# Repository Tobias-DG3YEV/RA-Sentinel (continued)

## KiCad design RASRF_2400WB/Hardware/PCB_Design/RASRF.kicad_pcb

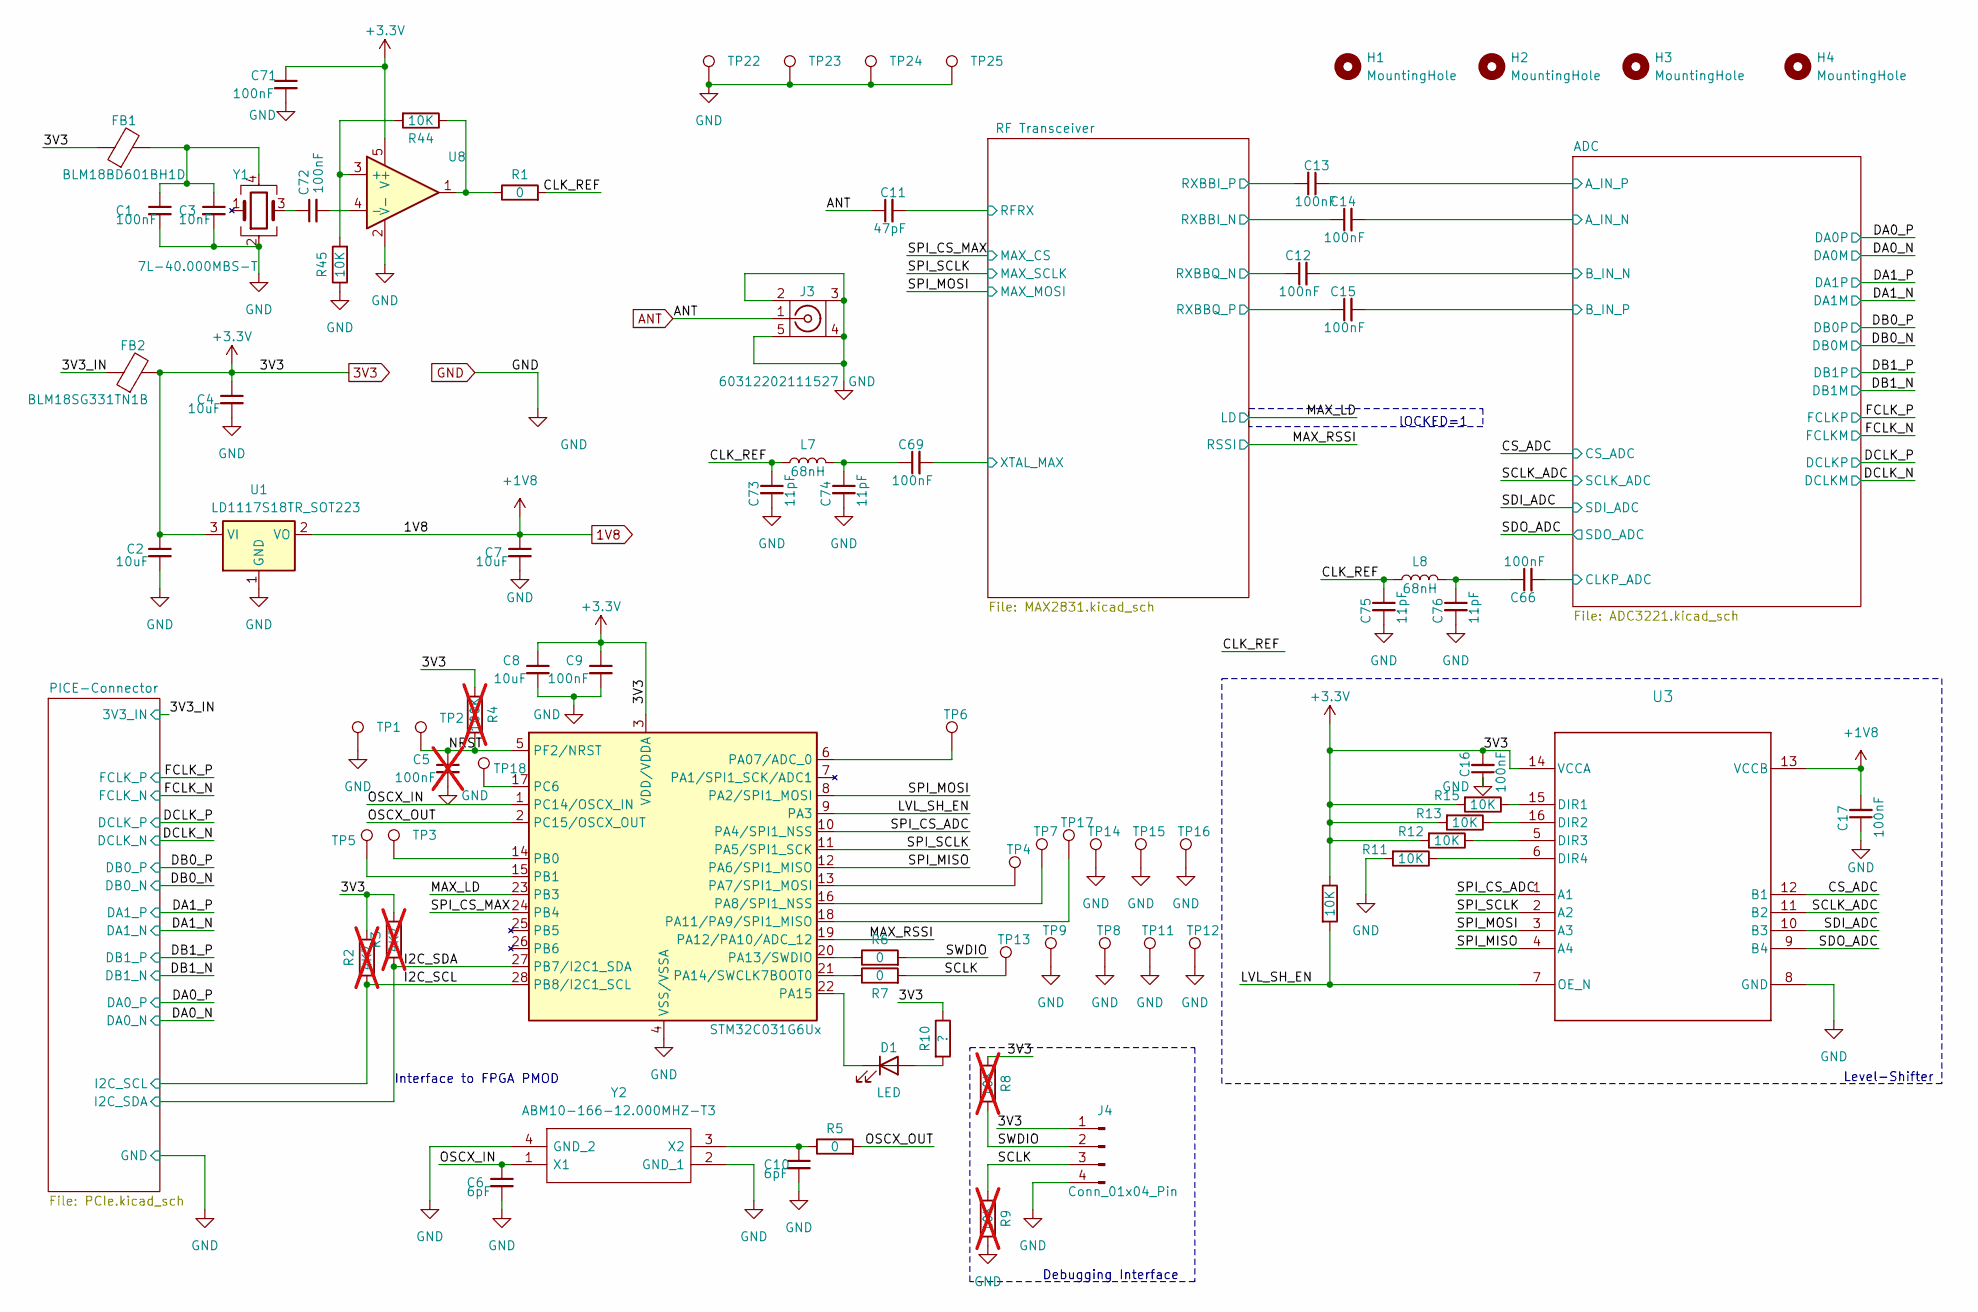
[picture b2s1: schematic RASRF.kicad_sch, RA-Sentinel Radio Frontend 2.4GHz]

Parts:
C1, C9, C12, C13, C14, C15, C16, C17, C66, C69, C71, C72: 100nF; C_0603_1608Metric
C2, C4, C7, C8: 10uF; C_0603_1608Metric
C3: 10nF; C_0603_1608Metric
C5: 100nF; C_0603_1608Metric; not fitted
C6, C10: 6pF; C_0603_1608Metric
C11: 47pF; C_0603_1608Metric
C73, C74, C75, C76: 11pF; C_0603_1608Metric
D1: LED; LED_0603_1608Metric
FB1: BLM18BD601BH1D; IND_BLM18_0603_MUR
FB2: BLM18SG331TN1B; IND_BLM18_0603_MUR
H1, H2, H3, H4: MountingHole; MountingHole_3.2mm_M3_ISO7380
J3: 60312202111527; JACK_02114307_WRE
J4: Conn_01x04_Pin; PinSocket_1x04_P2.54mm_Vertical
L7, L8: 68nH; L_0603_1608Metric
R1, R5, R6, R7: 0; R_0603_1608Metric
R2, R3: 4K7; R_0603_1608Metric; not fitted
R4: 100K; R_0603_1608Metric; not fitted
R8, R9: 10K; R_0603_1608Metric; not fitted
R10: ?; R_0603_1608Metric
R11, R12, R13, R14, R15, R44, R45: 10K; R_0603_1608Metric
TP1, TP8, TP11, TP12, TP14, TP15, TP16: TestPoint; TestPoint_THTPad_D1.0mm_Drill0.5mm
TP2, TP3, TP4, TP5, TP6, TP7, TP9, TP13, TP17, TP18: TestPoint; TestPoint_Pad_1.0x1.0mm
TP22, TP23, TP24, TP25: TestPoint; TestPoint_Pad_D1.5mm
U1: LD1117S18TR_SOT223; SOT-223-3_TabPin2
U2: STM32C031G6Ux; QFN-28_4x4mm_P0.5mm
U3: SN74AXC4T774RSVR; RSV0016A
U8: SOT-23-5
Y1: 7L-40.000MBS-T; 4-SMD_NoLead_Oscillator
Y2: ABM10-166-12.000MHZ-T3; ABM10; Mouser Part Number 815-ABM10-166-12T

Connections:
1V8: C7.1, C17.2, U1.2 (VO), U3.13 (VCCB); also elsewhere on the board
3V3: C2.1, C4.1, C8.1, C9.1, C16.2, C71.1, FB1.1, FB2.2, J4.1, R2.2, R3.1, R4.1, R8.1, R10.1, R12.2, R13.2, R14.1, R15.2, U1.3 (VI), U2.3 (VDD/VDDA), U3.14 (VCCA), U8.5 (V+); also elsewhere on the board
/3V3_IN: FB2.1; also elsewhere on the board
/ RF Transceiver/RFRX: C11.2; also elsewhere on the board
/ RF Transceiver/RXBBI_N: C14.1; also elsewhere on the board
/ RF Transceiver/RXBBI_P: C13.2; also elsewhere on the board
/ RF Transceiver/RXBBQ_N: C12.1; also elsewhere on the board
/ RF Transceiver/RXBBQ_P: C15.1; also elsewhere on the board
/ RF Transceiver/XTAL_MAX: C69.2; also elsewhere on the board
/ADC/A_IN_N: C14.2; also elsewhere on the board
/ADC/A_IN_P: C13.1; also elsewhere on the board
/ADC/B_IN_N: C12.2; also elsewhere on the board
/ADC/B_IN_P: C15.2; also elsewhere on the board
/ADC/CLKP_ADC: C66.2; also elsewhere on the board
/CLK_REF: C73.1, C75.1, L7.1, L8.1, R1.2
/CS_ADC: U3.12 (B1); also elsewhere on the board
/I2C_SCL: R2.1, U2.28 (PB8/I2C1_SCL); also elsewhere on the board
/I2C_SDA: R3.2, U2.27 (PB7/I2C1_SDA); also elsewhere on the board
/LVL_SH_EN: R14.2, U2.9 (PA3), U3.7 (OE_N)
/MAX_LD: U2.23 (PB3); also elsewhere on the board
/MAX_RSSI: U2.19 (PA12/PA10/ADC_12); also elsewhere on the board
/NRST: C5.1, R4.2, TP2.1, U2.5 (PF2/NRST)
/OSCX_IN: C6.1, U2.1 (PC14/OSCX_IN), Y2.1 (X1)
/OSCX_OUT: R5.2, U2.2 (PC15/OSCX_OUT)
/SCLK: J4.3, R7.2, R9.1, TP13.1
/SCLK_ADC: U3.11 (B2); also elsewhere on the board
/SDI_ADC: U3.10 (B3); also elsewhere on the board
/SDO_ADC: U3.9 (B4); also elsewhere on the board
/SPI_CS_ADC: U2.10 (PA4/SPI1_NSS), U3.1 (A1)
/SPI_CS_MAX: U2.24 (PB4); also elsewhere on the board
/SPI_MISO: U2.12 (PA6/SPI1_MISO), U3.4 (A4)
/SPI_MOSI: U2.8 (PA2/SPI1_MOSI), U3.3 (A3); also elsewhere on the board
/SPI_SCLK: U2.11 (PA5/SPI1_SCK), U3.2 (A2); also elsewhere on the board
/SWDIO: J4.2, R6.2, R8.2
ANT: C11.1, J3.1
GND: C1.2, C2.2, C3.2, C4.2, C5.2, C6.2, C7.2, C8.2, C9.2, C10.2, C16.1, C17.1, C71.2, C73.2, C74.2, C75.2, C76.2, J3.2, J3.3, J3.4, J3.5, J4.4, R9.2, R11.2, R45.1, TP1.1, TP8.1, TP9.1, TP11.1, TP12.1, TP14.1, TP15.1, TP16.1, TP22.1, TP23.1, TP24.1, TP25.1, U1.1 (GND), U2.4 (VSS/VSSA), U3.8 (GND), U8.2 (V-), Y1.2, Y2.2 (GND_1), Y2.4 (GND_2); also elsewhere on the board
unnamed: C1.1, C3.1, FB1.2, Y1.4
unnamed: C66.1, C76.1, L8.2
unnamed: C69.1, C74.1, L7.2
unnamed: C72.1, Y1.3
unnamed: D1.2 (A), R10.2
unnamed: D1.1 (K), U2.22 (PA15)
unnamed: R1.1, R44.1, U8.1
unnamed: TP6.1, U2.6 (PA07/ADC_0)
unnamed: TP4.1, U2.13 (PA7/SPI1_MOSI)
unnamed: TP7.1, U2.16 (PA8/SPI1_NSS)
unnamed: TP17.1, U2.18 (PA11/PA9/SPI1_MISO)
unnamed: R6.1, U2.20 (PA13/SWDIO)
unnamed: R7.1, U2.21 (PA14/SWCLK7BOOT0)
unnamed: TP3.1, U2.14 (PB0)
unnamed: TP5.1, U2.15 (PB1)
unnamed: TP18.1, U2.17 (PC6)
unnamed: R15.1, U3.15 (DIR1)
unnamed: R13.1, U3.16 (DIR2)
unnamed: R12.1, U3.5 (DIR3)
unnamed: R11.1, U3.6 (DIR4)
unnamed: R44.2, R45.2, U8.3 (+)
unnamed: C72.2, U8.4 (-)
unnamed: C10.1, R5.1, Y2.3 (X2)

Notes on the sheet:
Debugging Interface
Level-Shifter
Interface to FPGA PMOD
lOCKED=1

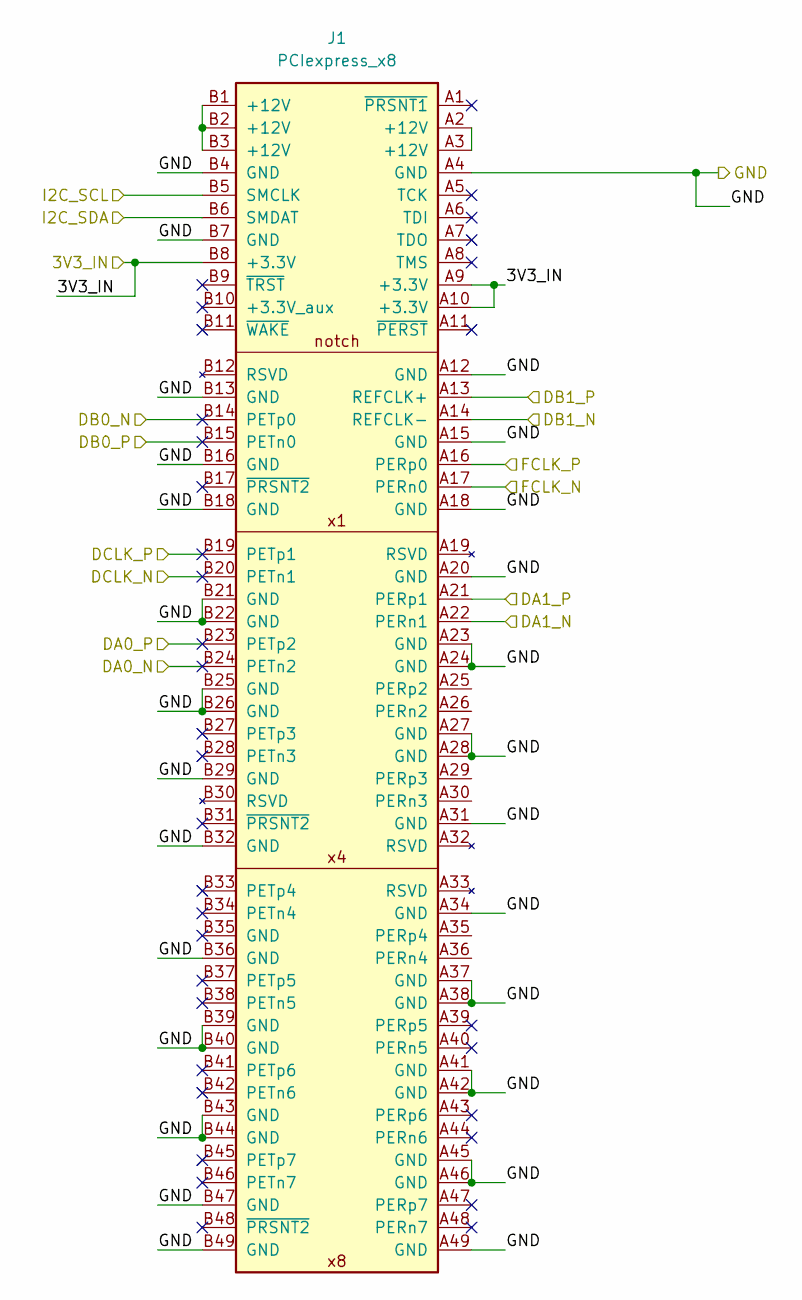
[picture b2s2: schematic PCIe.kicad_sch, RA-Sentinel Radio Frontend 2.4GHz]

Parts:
J1: PCIexpress_x8; BUS_PCIexpress_x8

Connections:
/3V3_IN: J1.A9 (+3.3V), J1.A10 (+3.3V), J1.B8 (+3.3V); also elsewhere on the board
/DA0_N: J1.B24 (PETn2); also elsewhere on the board
/DA0_P: J1.B23 (PETp2); also elsewhere on the board
/DA1_N: J1.A22 (PERn1); also elsewhere on the board
/DA1_P: J1.A21 (PERp1); also elsewhere on the board
/DB0_N: J1.B14 (PETp0); also elsewhere on the board
/DB0_P: J1.B15 (PETn0); also elsewhere on the board
/DB1_N: J1.A14 (REFCLK-); also elsewhere on the board
/DB1_P: J1.A13 (REFCLK+); also elsewhere on the board
/DCLK_N: J1.B20 (PETn1); also elsewhere on the board
/DCLK_P: J1.B19 (PETp1); also elsewhere on the board
/FCLK_N: J1.A17 (PERn0); also elsewhere on the board
/FCLK_P: J1.A16 (PERp0); also elsewhere on the board
/I2C_SCL: J1.B5 (SMCLK); also elsewhere on the board
/I2C_SDA: J1.B6 (SMDAT); also elsewhere on the board
GND: J1.A4 (GND), J1.A12 (GND), J1.A15 (GND), J1.A18 (GND), J1.A20 (GND), J1.A23 (GND), J1.A24 (GND), J1.A27 (GND), J1.A28 (GND), J1.A31 (GND), J1.A34 (GND), J1.A37 (GND), J1.A38 (GND), J1.A41 (GND), J1.A42 (GND), J1.A45 (GND), J1.A46 (GND), J1.A49 (GND), J1.B4 (GND), J1.B7 (GND), J1.B13 (GND), J1.B16 (GND), J1.B18 (GND), J1.B21 (GND), J1.B22 (GND), J1.B25 (GND), J1.B26 (GND), J1.B29 (GND), J1.B32 (GND), J1.B36 (GND), J1.B39 (GND), J1.B40 (GND), J1.B43 (GND), J1.B44 (GND), J1.B47 (GND), J1.B49 (GND); also elsewhere on the board
unnamed: J1.A2 (+12V), J1.A3 (+12V)
unnamed: J1.B1 (+12V), J1.B2 (+12V), J1.B3 (+12V)

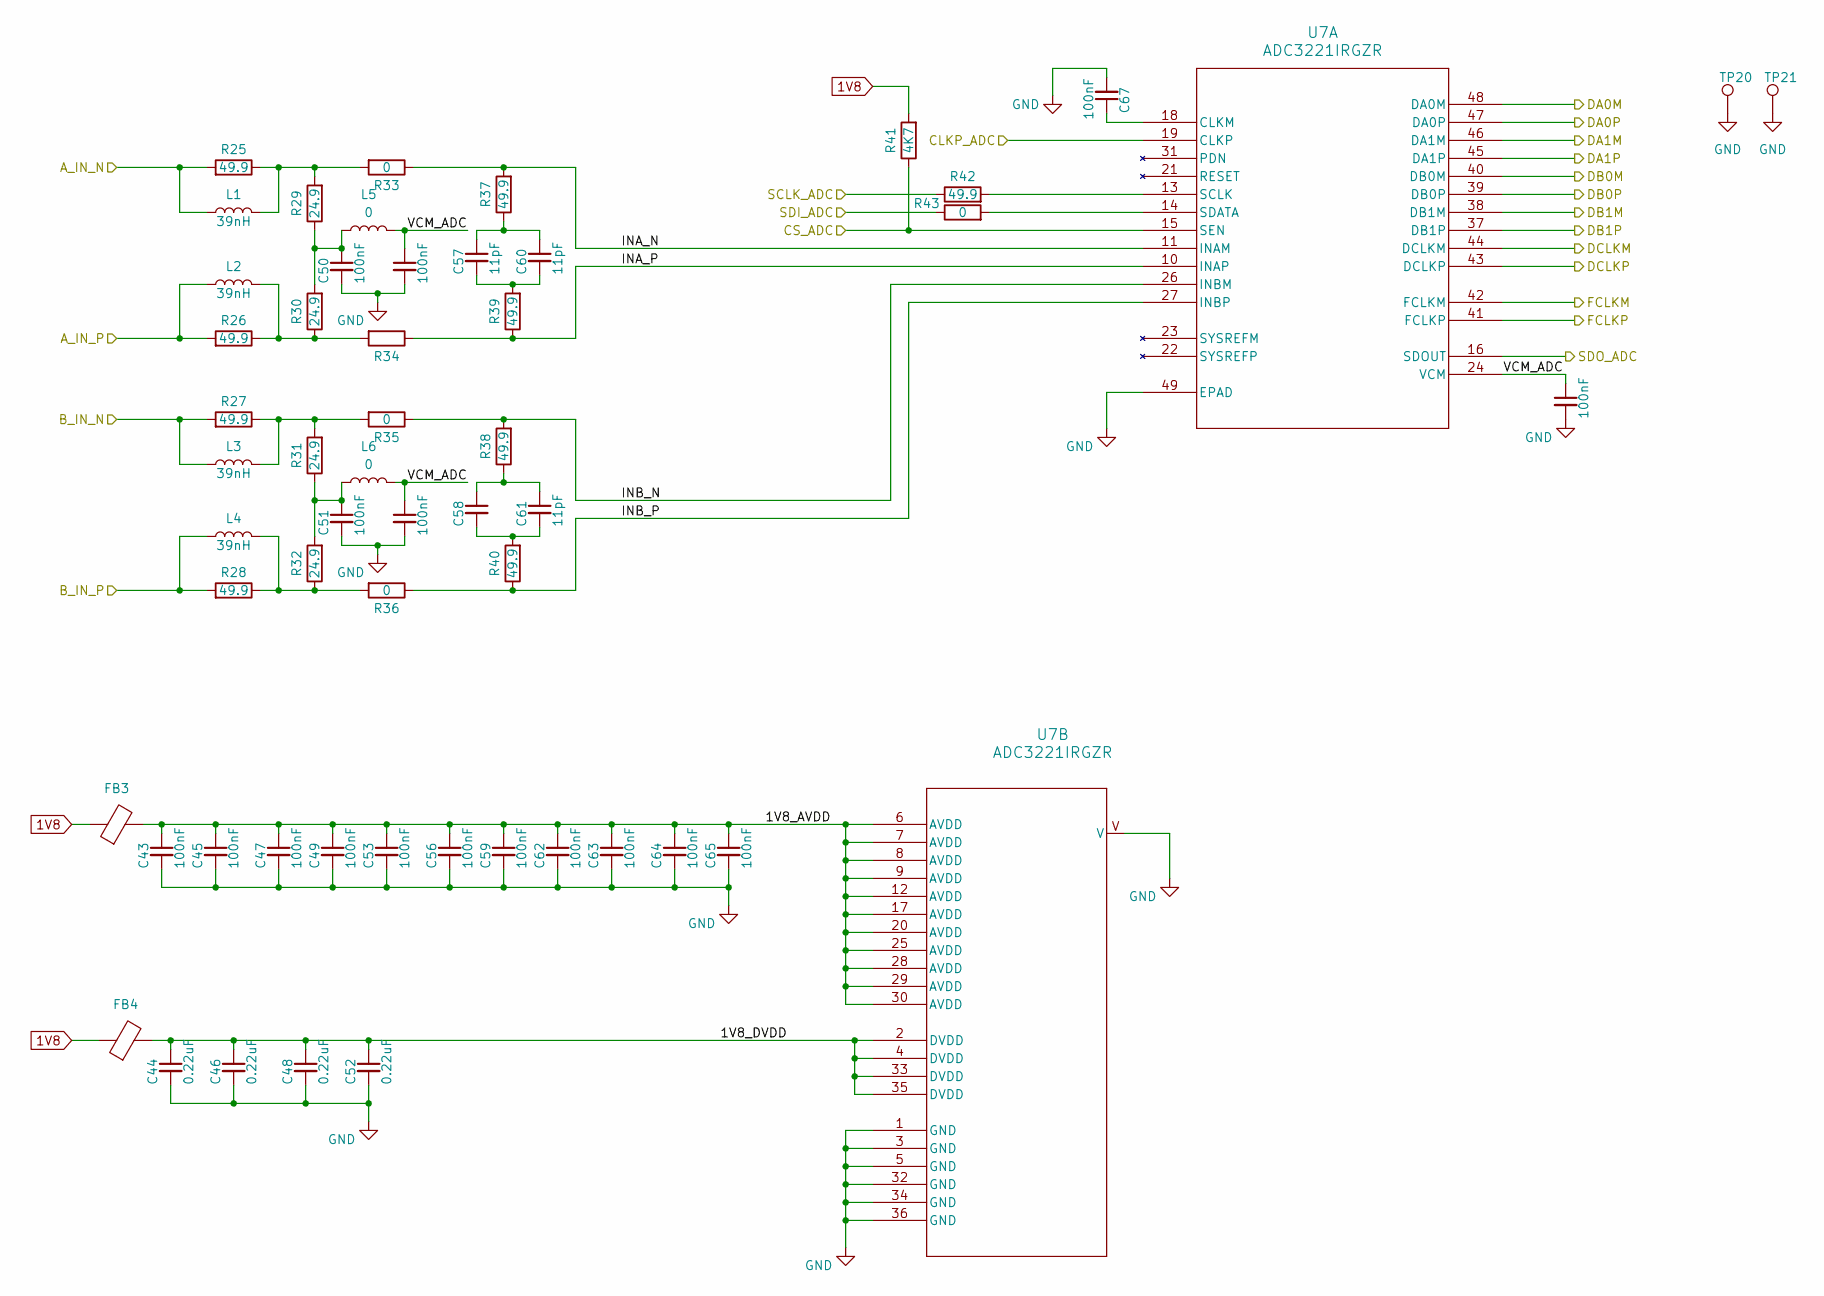
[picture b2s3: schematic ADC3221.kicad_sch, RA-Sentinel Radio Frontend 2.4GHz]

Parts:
C43, C45, C47, C49, C50, C51, C53, C54, C55, C56, C59, C62, C63, C64, C65, C67, C68: 100nF; C_0603_1608Metric
C44, C46, C48, C52: 0.22uF; C_0603_1608Metric
C57, C58, C60, C61: 11pF; C_0603_1608Metric
FB3, FB4: BLM41PG102SN1L; IND_BLM41_1806_MUR
L1, L2, L3, L4: 39nH; L_0603_1608Metric
L5, L6: 0; L_0603_1608Metric
R25, R26, R27, R28, R37, R38, R39, R40, R42: 49.9; R_0603_1608Metric
R29, R30, R31, R32: 24.9; R_0603_1608Metric
R33, R34, R35, R36, R43: 0; R_0603_1608Metric
R41: 4K7; R_0603_1608Metric
TP20, TP21: TestPoint; TestPoint_THTPad_D1.0mm_Drill0.5mm
U7: ADC3221IRGZR; RGZ48_TEX

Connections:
1V8: FB3.1, FB4.1, R41.2; also elsewhere on the board
/ADC/1V8_AVDD: C43.1, C45.1, C47.1, C49.1, C53.1, C56.1, C59.1, C62.1, C63.1, C64.1, C65.1, FB3.2, U7.6 (AVDD), U7.7 (AVDD), U7.8 (AVDD), U7.9 (AVDD), U7.12 (AVDD), U7.17 (AVDD), U7.20 (AVDD), U7.25 (AVDD), U7.28 (AVDD), U7.29 (AVDD), U7.30 (AVDD)
/ADC/1V8_DVDD: C44.1, C46.1, C48.1, C52.1, FB4.2, U7.2 (DVDD), U7.4 (DVDD), U7.33 (DVDD), U7.35 (DVDD)
/ADC/A_IN_N: L1.1, R25.2; also elsewhere on the board
/ADC/A_IN_P: L2.1, R26.2; also elsewhere on the board
/ADC/B_IN_N: L3.1, R27.2; also elsewhere on the board
/ADC/B_IN_P: L4.1, R28.2; also elsewhere on the board
/ADC/CLKP_ADC: U7.19 (CLKP); also elsewhere on the board
/ADC/INA_N: R33.1, R37.2, U7.11 (INAM)
/ADC/INA_P: R34.1, R39.1, U7.10 (INAP)
/ADC/INB_N: R35.1, R38.2, U7.26 (INBM)
/ADC/INB_P: R36.1, R40.1, U7.27 (INBP)
/ADC/VCM_ADC: C54.1, C55.1, C68.1, L5.2, L6.2, U7.24 (VCM)
/CS_ADC: R41.1, U7.15 (SEN); also elsewhere on the board
/DA0_N: U7.48 (DA0M); also elsewhere on the board
/DA0_P: U7.47 (DA0P); also elsewhere on the board
/DA1_N: U7.46 (DA1M); also elsewhere on the board
/DA1_P: U7.45 (DA1P); also elsewhere on the board
/DB0_N: U7.40 (DB0M); also elsewhere on the board
/DB0_P: U7.39 (DB0P); also elsewhere on the board
/DB1_N: U7.38 (DB1M); also elsewhere on the board
/DB1_P: U7.37 (DB1P); also elsewhere on the board
/DCLK_N: U7.44 (DCLKM); also elsewhere on the board
/DCLK_P: U7.43 (DCLKP); also elsewhere on the board
/FCLK_N: U7.42 (FCLKM); also elsewhere on the board
/FCLK_P: U7.41 (FCLKP); also elsewhere on the board
/SCLK_ADC: R42.1; also elsewhere on the board
/SDI_ADC: R43.1; also elsewhere on the board
/SDO_ADC: U7.16 (SDOUT); also elsewhere on the board
GND: C43.2, C44.2, C45.2, C46.2, C47.2, C48.2, C49.2, C50.2, C51.2, C52.2, C53.2, C54.2, C55.2, C56.2, C59.2, C62.2, C63.2, C64.2, C65.2, C67.2, C68.2, TP20.1, TP21.1, U7.1 (GND), U7.3 (GND), U7.5 (GND), U7.32 (GND), U7.34 (GND), U7.36 (GND), U7.49 (EPAD), U7.V; also elsewhere on the board
unnamed: C50.1, L5.1, R29.1, R30.2
unnamed: C51.1, L6.1, R31.1, R32.2
unnamed: C57.1, C60.1, R37.1
unnamed: C57.2, C60.2, R39.2
unnamed: C58.1, C61.1, R38.1
unnamed: C58.2, C61.2, R40.2
unnamed: L1.2, R25.1, R29.2, R33.2
unnamed: L2.2, R26.1, R30.1, R34.2
unnamed: L3.2, R27.1, R31.2, R35.2
unnamed: L4.2, R28.1, R32.1, R36.2
unnamed: C67.1, U7.18 (CLKM)
unnamed: R42.2, U7.13 (SCLK)
unnamed: R43.2, U7.14 (SDATA)

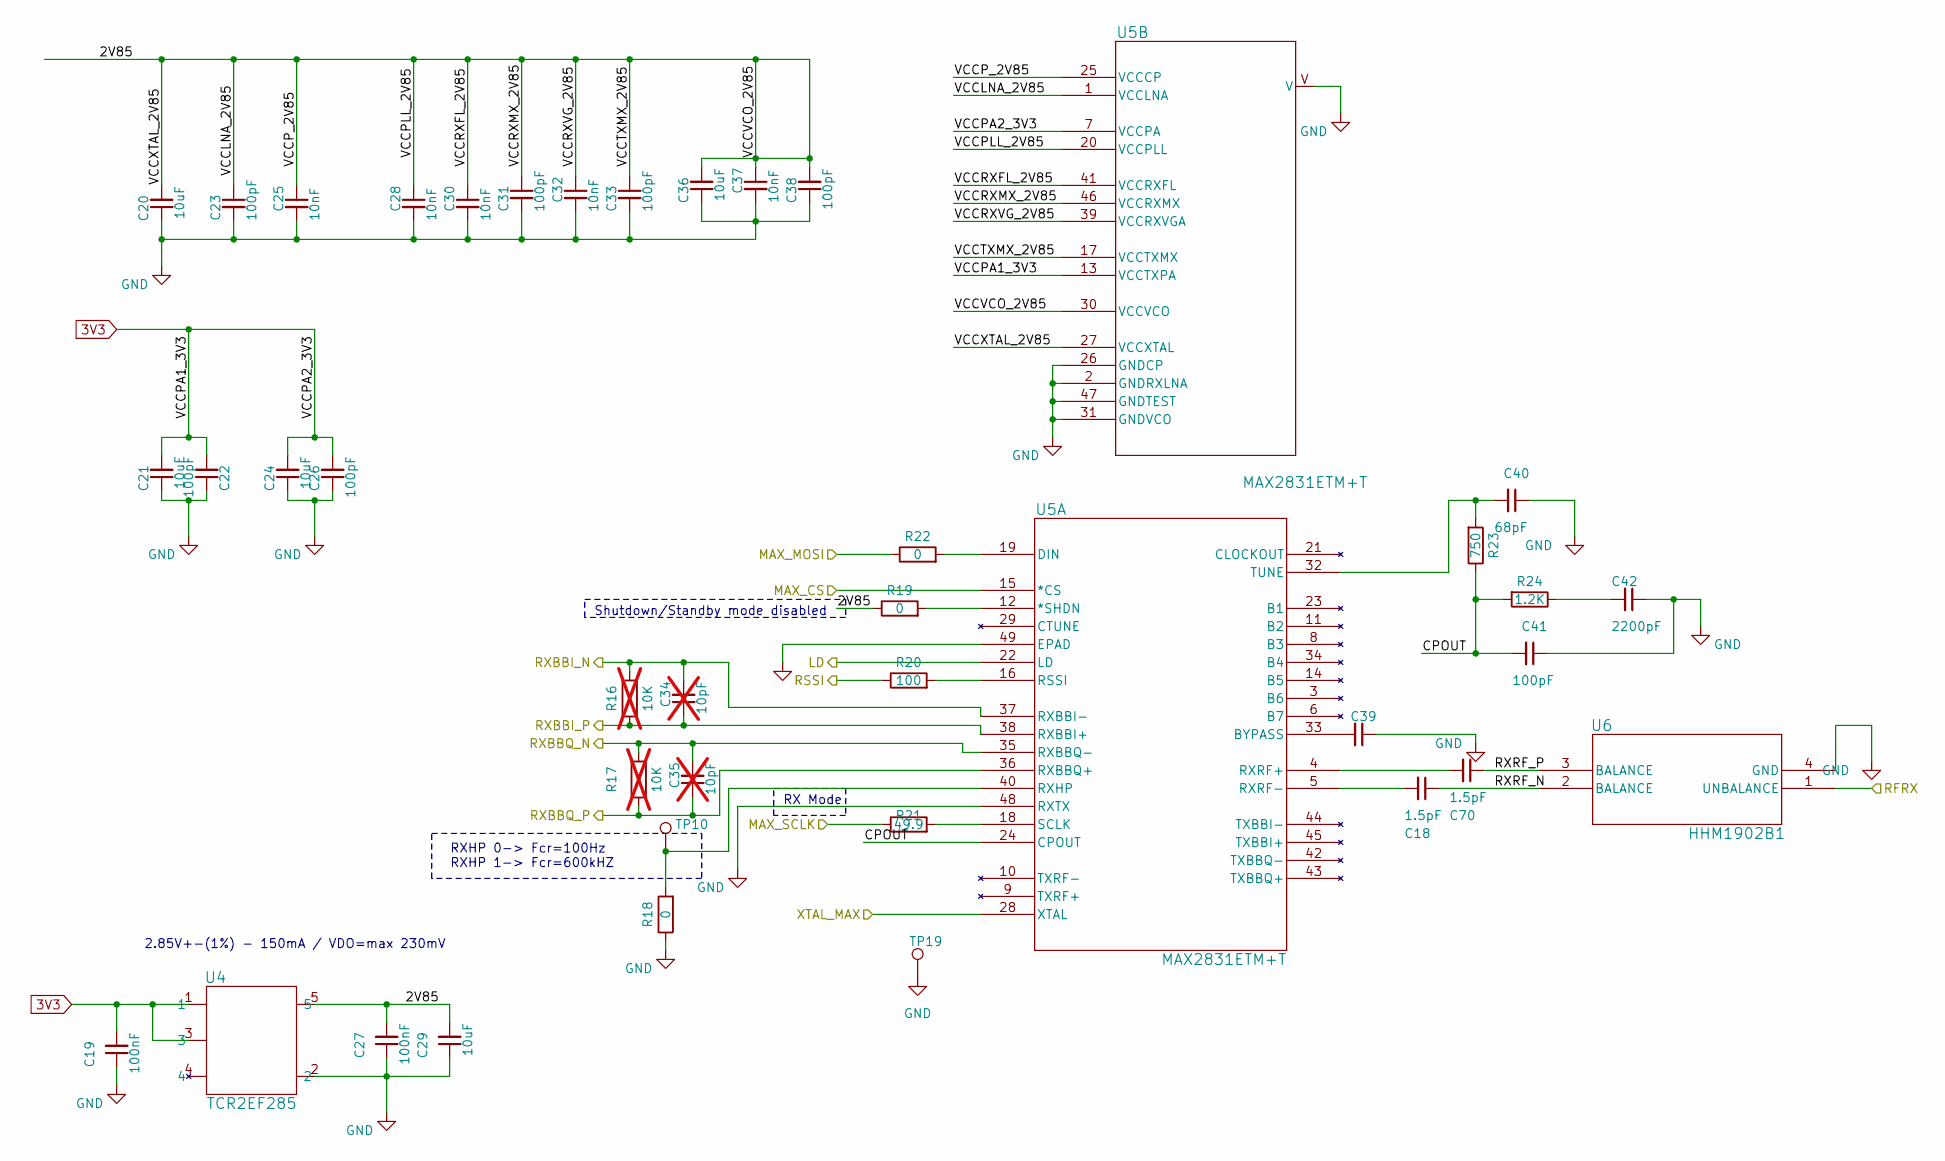
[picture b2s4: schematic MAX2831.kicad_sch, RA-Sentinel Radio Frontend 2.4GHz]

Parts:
C18, C70: 1.5pF; C_0603_1608Metric
C19, C27, C39: 100nF; C_0603_1608Metric
C20, C21, C24, C29, C36: 10uF; C_0603_1608Metric
C22, C23, C26, C31, C33, C38, C41: 100pF; C_0603_1608Metric
C25, C28, C30, C32, C37: 10nF; C_0603_1608Metric
C34, C35: 10pF; C_0603_1608Metric; not fitted
C40: 68pF; C_0603_1608Metric
C42: 2200pF; C_0603_1608Metric
R16, R17: 10K; R_0603_1608Metric; not fitted
R18, R19, R22: 0; R_0603_1608Metric
R20: 100; R_0603_1608Metric
R21: 49.9; R_0603_1608Metric
R23: 750; R_0603_1608Metric
R24: 1.2K; R_0603_1608Metric
TP10: TestPoint; TestPoint_Pad_1.0x1.0mm
TP19: TestPoint; TestPoint_Pad_D1.0mm
U4: TCR2EF285; SOT-25 SMV_TOS
U5: MAX2831ETM+T; 21-0144_T4877&plus_4_MXM
U6: HHM1902B1; HHM-4_1P0X0P5

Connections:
3V3: C19.2, C21.2, C22.2, C24.2, C26.2, U4.1, U4.3, U5.7 (VCCPA), U5.13 (VCCTXPA); also elsewhere on the board
/ RF Transceiver/2V85: C20.2, C23.1, C25.1, C27.2, C28.1, C29.2, C30.1, C31.1, C32.1, C33.1, C36.2, C37.1, C38.2, R19.1, U4.5, U5.1 (VCCLNA), U5.17 (VCCTXMX), U5.20 (VCCPLL), U5.25 (VCCCP), U5.27 (VCCXTAL), U5.30 (VCCVCO), U5.39 (VCCRXVGA), U5.41 (VCCRXFL), U5.46 (VCCRXMX)
/ RF Transceiver/CPOUT: C41.2, R23.1, R24.2, U5.24 (CPOUT)
/ RF Transceiver/RFRX: U6.1 (UNBALANCE); also elsewhere on the board
/ RF Transceiver/RXBBI_N: C34.2, R16.2, U5.37 (RXBBI-); also elsewhere on the board
/ RF Transceiver/RXBBI_P: C34.1, R16.1, U5.38 (RXBBI+); also elsewhere on the board
/ RF Transceiver/RXBBQ_N: C35.2, R17.2, U5.35 (RXBBQ-); also elsewhere on the board
/ RF Transceiver/RXBBQ_P: C35.1, R17.1, U5.36 (RXBBQ+); also elsewhere on the board
/ RF Transceiver/RXRF_N: C18.1, U6.2 (BALANCE)
/ RF Transceiver/RXRF_P: C70.1, U6.3 (BALANCE)
/ RF Transceiver/XTAL_MAX: U5.28 (XTAL); also elsewhere on the board
/MAX_LD: U5.22 (LD); also elsewhere on the board
/MAX_RSSI: R20.1; also elsewhere on the board
/SPI_CS_MAX: U5.15 (*CS); also elsewhere on the board
/SPI_MOSI: R22.1; also elsewhere on the board
/SPI_SCLK: R21.1; also elsewhere on the board
GND: C19.1, C20.1, C21.1, C22.1, C23.2, C24.1, C25.2, C26.1, C27.1, C28.2, C29.1, C30.2, C31.2, C32.2, C33.2, C36.1, C37.2, C38.1, C39.1, C40.1, C41.1, C42.1, R18.1, TP19.1, U4.2, U5.2 (GNDRXLNA), U5.26 (GNDCP), U5.31 (GNDVCO), U5.47 (GNDTEST), U5.48 (RXTX), U5.49 (EPAD), U5.V, U6.4 (GND); also elsewhere on the board
unnamed: C42.2, R24.1
unnamed: R19.2, U5.12 (*SHDN)
unnamed: C39.2, U5.33 (BYPASS)
unnamed: R22.2, U5.19 (DIN)
unnamed: R20.2, U5.16 (RSSI)
unnamed: R18.2, TP10.1, U5.40 (RXHP)
unnamed: C70.2, U5.4 (RXRF+)
unnamed: C18.2, U5.5 (RXRF-)
unnamed: R21.2, U5.18 (SCLK)
unnamed: C40.2, R23.2, U5.32 (TUNE)

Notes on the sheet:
2.85V+-(1%) - 150mA / VDO=max 230mV
Shutdown/Standby mode disabled
RX Mode
RXHP 0-> Fcr=100Hz RXHP 1-> Fcr=600kHZ

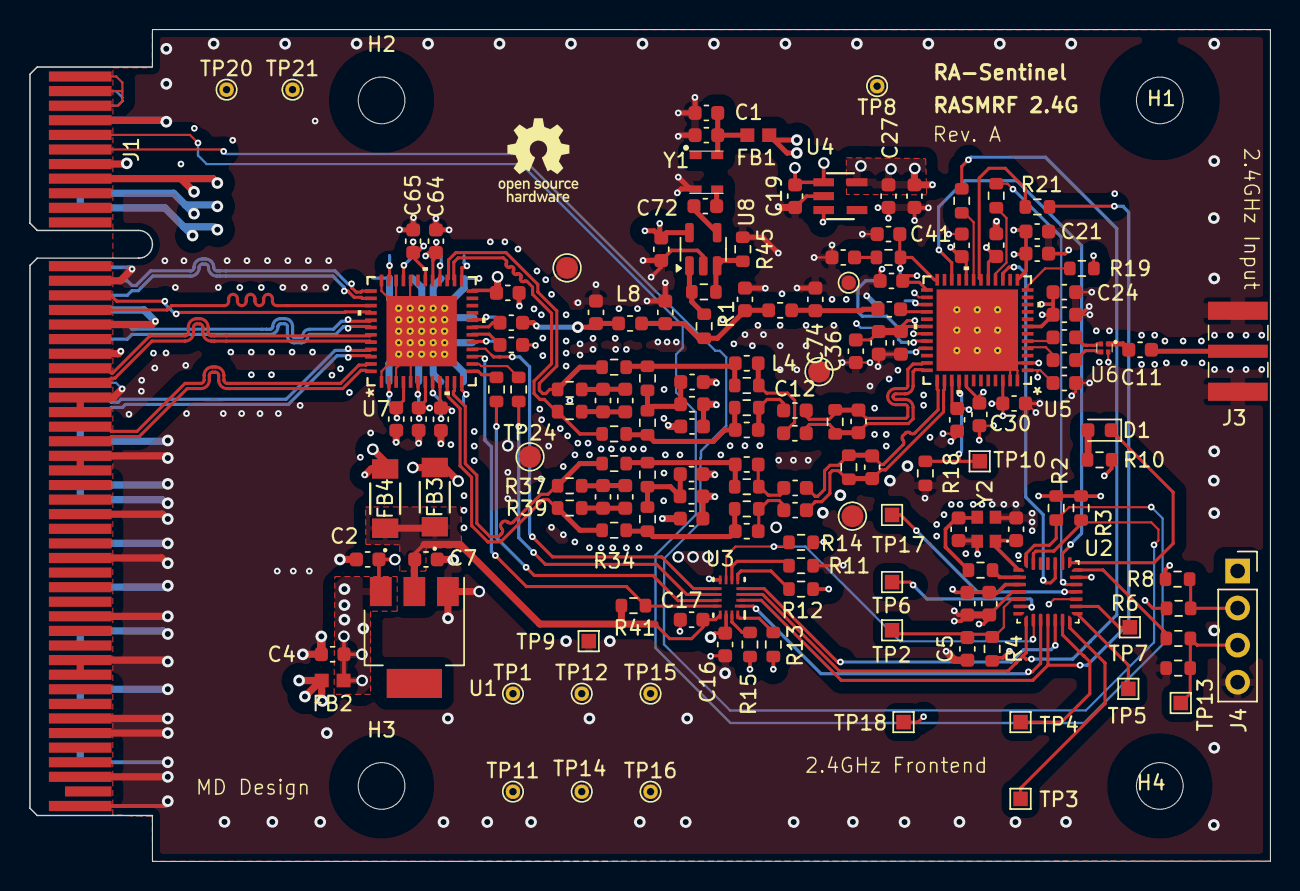
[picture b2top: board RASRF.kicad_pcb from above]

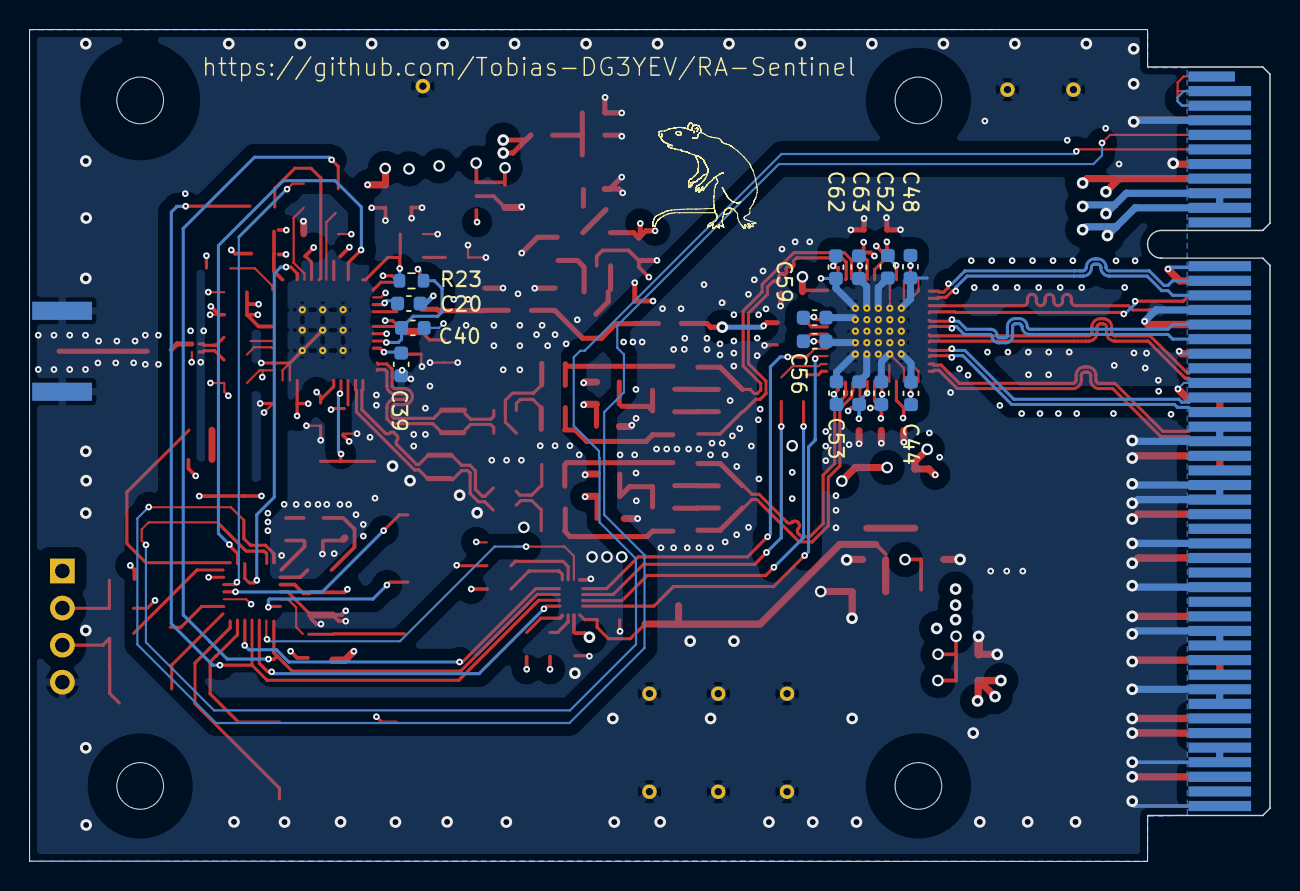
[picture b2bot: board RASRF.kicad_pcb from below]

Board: 4 copper layers, 85.0 x 57.0 mm, 176 parts (14 on the bottom side), 107 nets.

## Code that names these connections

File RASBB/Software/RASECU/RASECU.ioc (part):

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Mcu.Name=STM32H750VBTx
Mcu.Package=LQFP100
Mcu.UserName=STM32H750VBTx
PA1.Mode=RMII
PA1.Signal=ETH_REF_CLK
PA10.GPIOParameters=GPIO_Label
PA10.GPIO_Label=EN_MUX1
PA10.Signal=GPIO_Output
PA11.GPIOParameters=GPIO_Label
PA11.GPIO_Label=SPI2_NSS
PA11.Signal=GPIO_Output
PA13\ (JTMS/SWDIO).Mode=JTAG_4_pins
PA13\ (JTMS/SWDIO).Signal=DEBUG_JTMS-SWDIO
PA14\ (JTCK/SWCLK).Mode=JTAG_4_pins
PA14\ (JTCK/SWCLK).Signal=DEBUG_JTCK-SWCLK
PA15\ (JTDI).Mode=JTAG_4_pins
PA15\ (JTDI).Signal=DEBUG_JTDI
PA2.Mode=RMII
PA2.Signal=ETH_MDIO
PA3.GPIOParameters=GPIO_Label
PA3.GPIO_Label=ETH_NRST
PA3.Signal=GPIO_Output
PA4.GPIOParameters=GPIO_PuPd
PA4.GPIO_PuPd=GPIO_NOPULL
PA4.Mode=Slave_8_bits_External_Synchro
PA4.Signal=DCMI_HSYNC
PA5.Signal=COMP_DAC12_group
PA6.Mode=Slave_8_bits_External_Synchro
PA6.Signal=DCMI_PIXCLK
PA7.Mode=RMII
PA7.Signal=ETH_CRS_DV
PA8.Mode=I2C
PA8.Signal=I2C3_SCL
PA9.GPIOParameters=GPIO_Label
PA9.GPIO_Label=EN_MUX2
PA9.Signal=GPIO_Output
PB0.GPIOParameters=GPIO_Label
PB0.GPIO_Label=CS_MUX2
PB0.Signal=GPIO_Output
PB1.Signal=ADCx_INP5
PB10.Mode=Full_Duplex_Master
PB10.Signal=SPI2_SCK
PB11.Mode=RMII
PB11.Signal=ETH_TX_EN
PB12.Mode=RMII
PB12.Signal=ETH_TXD0
PB13.Mode=RMII
PB13.Signal=ETH_TXD1
PB14.Mode=Full_Duplex_Master
PB14.Signal=SPI2_MISO
PB15.GPIOParameters=GPIO_Label
PB15.GPIO_Label=CS_MUX1
PB15.Signal=GPIO_Output
PB2.Mode=Full_Duplex_Master
PB2.Signal=SPI3_MOSI
PB3\ (JTDO/TRACESWO).Mode=JTAG_4_pins
PB3\ (JTDO/TRACESWO).Signal=DEBUG_JTDO-SWO
PB4\ (NJTRST).GPIOParameters=GPIO_Label
PB4\ (NJTRST).GPIO_Label=FPGA01_PROG
PB4\ (NJTRST).Signal=GPIO_Output
PB5.GPIOParameters=GPIO_Label
PB5.GPIO_Label=FPGA02_PROG
PB5.Signal=GPIO_Output
PB6.GPIOParameters=GPIO_Pu
PB6.GPIO_Pu=GPIO_PULLUP
PB6.Mode=I2C
PB6.Signal=I2C1_SCL
PB7.Mode=Slave_8_bits_External_Synchro
PB7.Signal=DCMI_VSYNC
PB9.Mode=I2C
PB9.Signal=I2C1_SDA
PC0.GPIOParameters=GPIO_Label
PC0.GPIO_Label=uC_CONFIG
PC0.Signal=GPIO_Input
PC1.Mode=RMII
PC1.Signal=ETH_MDC
PC10.Mode=Full_Duplex_Master
PC10.Signal=SPI3_SCK
PC11.Mode=Full_Duplex_Master
PC11.Signal=SPI3_MISO
PC12.GPIOParameters=GPIO_Label
PC12.GPIO_Label=SPI4_NCS2
PC12.Signal=GPIO_Output
PC13.GPIOParameters=GPIO_Label
PC13.GPIO_Label=LORA_NRST
PC13.Signal=GPIO_Output
PC14-OSC32_IN\ (OSC32_IN).GPIOParameters=GPIO_Label
PC14-OSC32_IN\ (OSC32_IN).GPIO_Label=LORA_BUSY
PC14-OSC32_IN\ (OSC32_IN).Signal=GPIO_Input
PC15-OSC32_OUT\ (OSC32_OUT).GPIOParameters=GPIO_Label
PC15-OSC32_OUT\ (OSC32_OUT).GPIO_Label=LORA_DIO3
PC15-OSC32_OUT\ (OSC32_OUT).Signal=GPIO_Input
PC3_C.Mode=Full_Duplex_Master
PC3_C.Signal=SPI2_MOSI
PC4.Mode=RMII
PC4.Signal=ETH_RXD0
PC5.Mode=RMII
PC5.Signal=ETH_RXD1
PC6.Mode=Slave_8_bits_External_Synchro
PC6.Signal=DCMI_D0
PC7.Mode=Slave_8_bits_External_Synchro
PC7.Signal=DCMI_D1
PC8.Mode=Slave_8_bits_External_Synchro
PC8.Signal=DCMI_D2
PC9.Mode=I2C
PC9.Signal=I2C3_SDA
PD0.GPIOParameters=GPIO_Label
PD0.GPIO_Label=PD0_DEBUG
PD0.Signal=GPIO_Output
PD1.GPIOParameters=GPIO_Label
PD1.GPIO_Label=PD1_DEBUG
PD1.Signal=GPIO_Output
PD10.GPIOParameters=GPIO_Label
PD10.GPIO_Label=PD10_DEBUG
PD10.Signal=GPIO_Output
PD11.GPIOParameters=GPIO_Label
PD11.GPIO_Label=ALARM
PD11.Signal=GPIO_Output
PD12.GPIOParameters=GPIO_Label
PD12.GPIO_Label=PD12_DEBUG
PD12.Signal=GPIO_Output
PD13.GPIOParameters=GPIO_Label
PD13.GPIO_Label=PD13_DEBUG
PD13.Signal=GPIO_Output
PD14.GPIOParameters=GPIO_Label
PD14.GPIO_Label=PD14_DEBUG
PD14.Signal=GPIO_Output
PD15.GPIOParameters=GPIO_Label
PD15.GPIO_Label=PD15_DEBUG
PD15.Signal=GPIO_Output
PD2.GPIOParameters=GPIO_Label
PD2.GPIO_Label=PD2_DEBUG
PD2.Signal=GPIO_Output
PD3.Mode=Slave_8_bits_External_Synchro
PD3.Signal=DCMI_D5
PD4.GPIOParameters=GPIO_Label
PD4.GPIO_Label=PD4_DEBUG
PD4.Signal=GPIO_Output
PD7.GPIOParameters=GPIO_Label
PD7.GPIO_Label=PD7_DEBUG
PD7.Signal=GPIO_Output
PD8.Mode=Asynchronous
PD8.Signal=USART3_TX
PD9.Mode=Asynchronous
PD9.Signal=USART3_RX
PE1.Mode=Slave_8_bits_External_Synchro
PE1.Signal=DCMI_D3
PE10.GPIOParameters=GPIO_Label
PE10.GPIO_Label=LED_7
PE10.Signal=GPIO_Output
PE11.GPIOParameters=GPIO_Label
PE11.GPIO_Label=SPI4_NSS
PE11.Signal=GPIO_Output
PE12.Mode=Full_Duplex_Master
PE12.Signal=SPI4_SCK
PE13.Mode=Full_Duplex_Master
PE13.Signal=SPI4_MISO
PE14.Mode=Full_Duplex_Master
PE14.Signal=SPI4_MOSI
PE15.GPIOParameters=GPIO_Label
PE15.GPIO_Label=uC_PE15
PE15.Signal=GPIO_Output
PE2.GPIOParameters=GPIO_Label
PE2.GPIO_Label=LORA_DIO1
PE2.Signal=GPIO_Input
PE3.GPIOParameters=GPIO_Label
PE3.GPIO_Label=LORA_DIO2
PE3.Signal=GPIO_Input
PE4.Mode=Slave_8_bits_External_Synchro
PE4.Signal=DCMI_D4
PE5.Mode=Slave_8_bits_External_Synchro
PE5.Signal=DCMI_D6
PE6.Mode=Slave_8_bits_External_Synchro
PE6.Signal=DCMI_D7
PE7.GPIOParameters=GPIO_Label
PE7.GPIO_Label=SPI3_NSS
PE7.Signal=GPIO_Output
PE8.GPIOParameters=GPIO_Label
PE8.GPIO_Label=LED_9
PE8.Signal=GPIO_Output
PE9.GPIOParameters=GPIO_Label
PE9.GPIO_Label=LED_8
PE9.Signal=GPIO_Output
PH0-OSC_IN\ (PH0).Mode=HSE-External-Oscillator
PH0-OSC_IN\ (PH0).Signal=RCC_OSC_IN
PH1-OSC_OUT\ (PH1).Mode=HSE-External-Oscillator
PH1-OSC_OUT\ (PH1).Signal=RCC_OSC_OUT
RCC.HSE_VALUE=20000000
RCC.SYSCLKFreq_VALUE=480000000
RCC.SYSCLKSource=RCC_SYSCLKSOURCE_PLLCLK
board=custom

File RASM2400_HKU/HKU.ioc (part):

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Mcu.Name=STM32C031G(4-6)Ux
Mcu.Package=UFQFPN28
Mcu.UserName=STM32C031G6Ux
PA0.Mode=Asynchronous
PA0.Signal=USART1_TX
PA1.Mode=Asynchronous
PA1.Signal=USART1_RX
PA12\ [PA10].GPIOParameters=GPIO_Label
PA12\ [PA10].GPIO_Label=MAX_RSSI
PA12\ [PA10].Mode=IN12
PA12\ [PA10].Signal=ADC1_IN12
PA13.Mode=Serial_Wire
PA13.Signal=DEBUG_SWDIO
PA14-BOOT0.Mode=Serial_Wire
PA14-BOOT0.Signal=DEBUG_SWCLK
PA15.GPIOParameters=GPIO_Label
PA15.GPIO_Label=LED_PIN
PA15.Signal=GPIO_Output
PA2.Mode=Full_Duplex_Master
PA2.Signal=SPI1_MOSI
PA3.GPIOParameters=GPIO_Label
PA3.GPIO_Label=LVL_SH_EN
PA3.Signal=GPIO_Output
PA4.GPIOParameters=GPIO_Label
PA4.GPIO_Label=ADC_NCS
PA4.Signal=GPIO_Output
PA5.Mode=Full_Duplex_Master
PA5.Signal=SPI1_SCK
PA6.Mode=Full_Duplex_Master
PA6.Signal=SPI1_MISO
PB3.GPIOParameters=GPIO_Label
PB3.GPIO_Label=MAX_LD
PB3.Signal=GPXTI3
PB6.Mode=I2C
PB6.Signal=I2C1_SCL
PB7.Mode=I2C
PB7.Signal=I2C1_SDA
PC14-OSCX_IN\ (PC14).Mode=HSE-External-Oscillator-REMAPPED
PC14-OSCX_IN\ (PC14).Signal=RCC_OSCX_IN
PC15-OSCX_OUT\ (PC15).Mode=HSE-External-Oscillator-REMAPPED
PC15-OSCX_OUT\ (PC15).Signal=RCC_OSCX_OUT
RCC.HSE_VALUE=12000000
RCC.SYSCLKFreq_VALUE=12000000
RCC.SYSCLKSource=RCC_SYSCLKSOURCE_HSE
board=custom

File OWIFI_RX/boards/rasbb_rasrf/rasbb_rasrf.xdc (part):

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############## SPI (STM32H743 is master; quasi-static config only) ##########
# There is NO dedicated uC<->FPGA1 SPI on RASBB: the runtime channel is the
# SHARED FLASH BUS (RASBB.kicad_pcb): the uC's flash SPI lands on FPGA1 user
# pins SCK=D18 (SCK_FLASH_uC), SI/COPI=E17, SO/CIPO=D17, and the uC's flash
# select CS_FLASH_uC=E18 doubles as the FPGA1 select - the TS3A5018 mux
# (IC6, MUX_EN1/SWITCH_FLASH_1 from the uC) steers the flash on or off the
# bus. Firmware discipline: park the mux away from the flash before talking
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# flash traffic never sees contention on D17.
# (FPGA1_CLK/MOSI/MISO at E9/K17/K18 are the uC's CONFIGURATION path - E9
# is the dedicated CCLK ball, not LOCable by user logic.)
set_property PACKAGE_PIN D18 [get_ports SPI_sclk]
set_property PACKAGE_PIN E17 [get_ports SPI_copi]
set_property PACKAGE_PIN D17 [get_ports SPI_cipo]
set_property PACKAGE_PIN E18 [get_ports SPI_ncs]
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# and +1V8 - it is a leftover from the Wukong devboard and would collide with
# ADC_chA_N (E1) and ADC_chB_N (G2). See [rasbb-pcb-net-desync]: derive pins
# from the .kicad_pcb, never from a stale constraint set.
#   U10 A13/A14 = HDMI_CLK_P/N, B16/B17 = D0, A15/A16 = D1, B18/A18 = D2
set_property PACKAGE_PIN A13 [get_ports TMDS_clk_p]
set_property PACKAGE_PIN A14 [get_ports TMDS_clk_n]
set_property PACKAGE_PIN B16 [get_ports {TMDS_data_p[0]}]
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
